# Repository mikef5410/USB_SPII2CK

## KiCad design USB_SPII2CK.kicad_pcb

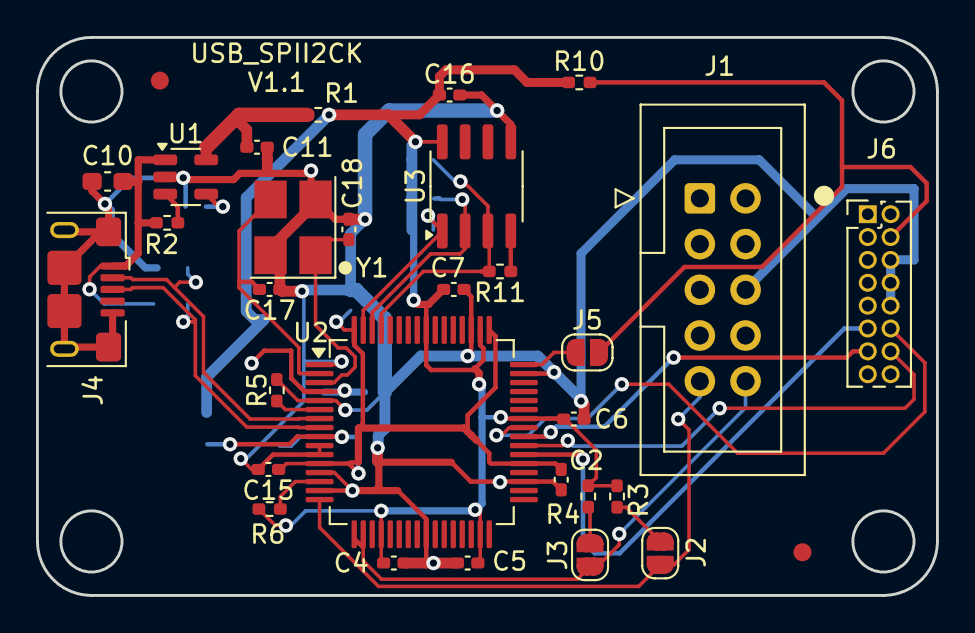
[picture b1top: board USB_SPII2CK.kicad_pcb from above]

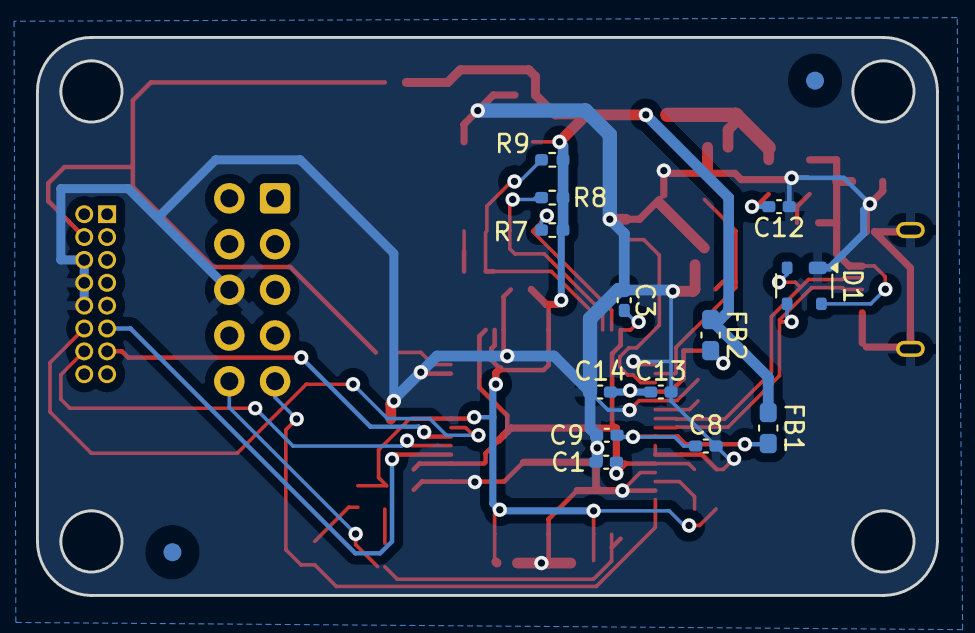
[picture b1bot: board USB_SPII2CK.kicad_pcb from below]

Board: 2 copper layers, 50.0 x 31.0 mm, 46 parts (15 on the bottom side), 29 nets.

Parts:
C1, C2, C3, C4, C5, C6, C7, C9, C12, C14, C16: 0.1u; C_0402_1005Metric_Pad0.74x0.62mm_HandSolder
C8, C13, C15: 3.3u; C_0402_1005Metric_Pad0.74x0.62mm_HandSolder
C10: 1u; C_0603_1608Metric_Pad1.08x0.95mm_HandSolder
C11: 4.7u; C_0402_1005Metric_Pad0.74x0.62mm_HandSolder
C17, C18: 27pF; C_0402_1005Metric_Pad0.74x0.62mm_HandSolder
D1: PRTR5V0U2X; SOT-143
FB1, FB2: MMZ1608Y102B; C_0603_1608Metric_Pad1.08x0.95mm_HandSolder
FID1, FID2, FID3, FID4: Fiducial; Fiducial_1mm_Mask3mm
J1: Conn_02x05_Odd_Even; IDC-Header_2x05_P2.54mm_Vertical
J2, J3, J5: Conn_01x02; SolderJumper-2_P1.3mm_Open_RoundedPad1.0x1.5mm
J4: USB_B_Micro; USB_Micro-B_Amphenol_10118193-0001LF_Horizontal
J6: Conn_02x08_Odd_Even; PinHeader_2x08_P1.27mm_Vertical
R1: 0; R_0402_1005Metric_Pad0.72x0.64mm_HandSolder
R2, R6, R7, R8, R9, R10: 10k; R_0402_1005Metric_Pad0.72x0.64mm_HandSolder
R3, R4: 5.11k; R_0402_1005Metric_Pad0.72x0.64mm_HandSolder
R5: 12.1k; R_0402_1005Metric_Pad0.72x0.64mm_HandSolder
R11: 2.15k; R_0402_1005Metric_Pad0.72x0.64mm_HandSolder
U1: LP2985-3.3; SOT-23-5
U2: FT2232HL; LQFP-64_10x10mm_P0.5mm
U3: AT93C46DN-SH-T; SOIC-8_3.9x4.9mm_P1.27mm
Y1: 12.00 MHz; Crystal_SMD_SeikoEpson_FA238V-4Pin_3.2x2.5mm_HandSoldering

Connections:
+3.3V: C4.2, C5.2, C6.2, C7.2, C16.1, FB1.1, FB2.1, R1.2, R3.2, R4.2, R6.1, R7.2, R8.2, R9.2, R10.1, U2.20 (VCCIO), U2.31 (VCCIO), U2.42 (VCCIO), U2.50 (VREGIN), U2.56 (VCCIO), U3.8 (VCC)
/I2C_SCL: J1.9, J2.1, U2.16 (ADBUS0)
/I2C_SDA: J1.10, J3.1, U2.17 (ADBUS1), U2.18 (ADBUS2)
/SPI_MISO: J6.13, U2.40 (BDBUS2)
/SPI_MOSI: J6.14, U2.39 (BDBUS1)
/SPI_SCK: J6.11, U2.38 (BDBUS0)
/SPI_SSN: J6.12, U2.41 (BDBUS3)
/USB+: D1.3 (I/O2), J4.3 (D+), U2.8 (DP)
/USB-: D1.2 (I/O1), J4.2 (D-), U2.7 (DM)
/~RESET: J5.2, J6.4, R10.2
GND: C1.1, C2.1, C3.1, C4.1, C5.1, C6.1, C7.1, C8.2, C9.1, C10.1, C11.1, C12.1, C13.2, C14.1, C15.2, C16.2, C17.1, C18.1, D1.1 (GND), J1.6, J4.5 (GND), J4.6 (Shield), J6.6, J6.8, J6.10, R5.1, U1.2 (GND), U2.1 (GND), U2.5 (GND), U2.10 (AGND), U2.11 (GND), U2.13 (TEST), U2.15 (GND), U2.25 (GND), U2.35 (GND), U2.47 (GND), U2.51 (GND), U3.5 (GND), Y1.2, Y1.4
unnamed: J2.2, R3.1
unnamed: J3.2, R4.1
unnamed: J5.1, U2.48 (BCBUS0)
unnamed: C12.2, U1.4 (BP)
unnamed: R2.2, U1.3 (ON/~OFF)
unnamed: C11.2, R1.1, U1.5 (VOUT)
unnamed: R8.1, U2.62 (EECLK), U3.2 (SCLK)
unnamed: R7.1, U2.63 (EECS), U3.1 (CS)
unnamed: R9.1, R11.2, U2.61 (EEDATA), U3.3 (DI)
unnamed: C17.2, U2.2 (OSCI), Y1.3
unnamed: C18.2, U2.3 (OSCO), Y1.1
unnamed: R5.2, U2.6 (REF)
unnamed: C13.1, C14.2, FB2.2, U2.4 (VPHY)
unnamed: C8.1, C9.2, FB1.2, U2.9 (VPLL)
unnamed: C1.2, C2.2, C3.2, C15.1, U2.12 (VCORE), U2.37 (VCORE), U2.49 (VREGOUT), U2.64 (VCORE)
unnamed: R6.2, U2.14 (~RESET)
unnamed: R11.1, U3.4 (DO)
VBUS: C10.2, D1.4 (VCC), J4.1 (VBUS), R2.1, U1.1 (VIN)

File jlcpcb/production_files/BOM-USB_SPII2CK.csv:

Comment,Designator,Footprint,LCSC
4.7u,C11,C_0402_1005Metric_Pad0.74x0.62mm_HandSolder,C106859
27pF,"C17,C18",C_0402_1005Metric_Pad0.74x0.62mm_HandSolder,C107002
MMZ1608Y102B,"FB1,FB2",C_0603_1608Metric_Pad1.08x0.95mm_HandSolder,C114771
LP2985-3.3,U1,SOT-23-5,C129375
USB_B_Micro,J4,USB_Micro-B_Amphenol_10118193-0001LF_Horizontal,C132562
12.1k,R5,R_0402_1005Metric_Pad0.72x0.64mm_HandSolder,C144800
1u,C10,C_0603_1608Metric_Pad1.08x0.95mm_HandSolder,C15849
0,R1,R_0402_1005Metric_Pad0.72x0.64mm_HandSolder,C17168
Conn_02x08_Odd_Even,J6,PinHeader_2x08_P1.27mm_Vertical,C17282974
10k,"R10,R2,R6,R7,R8,R9",R_0402_1005Metric_Pad0.72x0.64mm_HandSolder,C25744
2.15k,R11,R_0402_1005Metric_Pad0.72x0.64mm_HandSolder,C25878
FT2232HL,U2,LQFP-64_10x10mm_P0.5mm,C27882
PRTR5V0U2X,D1,SOT-143,C2827688
5.11k,"R3,R4",R_0402_1005Metric_Pad0.72x0.64mm_HandSolder,C310235
0.1u,"C1,C12,C14,C16,C2,C3,C4,C5,C6,C7,C9",C_0402_1005Metric_Pad0.74x0.62mm_HandSolder,C5142567
Conn_02x05_Odd_Even,J1,IDC-Header_2x05_P2.54mm_Vertical,C5665
AT93C46DN-SH-T,U3,SOIC-8_3.9x4.9mm_P1.27mm,C6499
3.3u,"C13,C15,C8",C_0402_1005Metric_Pad0.74x0.62mm_HandSolder,C695126
12.00 MHz,Y1,Crystal_SMD_SeikoEpson_FA238V-4Pin_3.2x2.5mm_HandSoldering,C9002

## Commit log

2024-07-22 Initial
2024-08-05 Add mechanicals.
2024-08-06 Add a simple bottom half-case.
2024-09-11 Add pdfs
2024-10-08 Update to V1.1 (move R10 out from under connector)
